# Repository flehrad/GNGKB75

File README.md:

# GNGKB75
This keyboard layout was created by goodnewsgeorge, inspired by the Eve Meteor keyboard

PCB work by flehrad

If you are producing this PCB package, it would be appreciated for attribution/crediting.

If you like this project, please consider support to The Board Podcast :)

GNGKB75_Rev0.zip is the Gerber package for production (not yet confirmed to be 100% working!)

All of the KiCAD project is in this repository including original screen images.

KiCAD v5.02-1 build was used to create this project.

Bill of materials required:

1x Elite-C microcontroller

1x Angled reset switch (MJT01117)

1x 7u stabiliser 

2x 2u stabilisers

74x 1N4148 Diode

74x MX Switches

Optional:

1x Rotary Encoder

RGB Lighting Strips (with Data/GND/VCC connections)

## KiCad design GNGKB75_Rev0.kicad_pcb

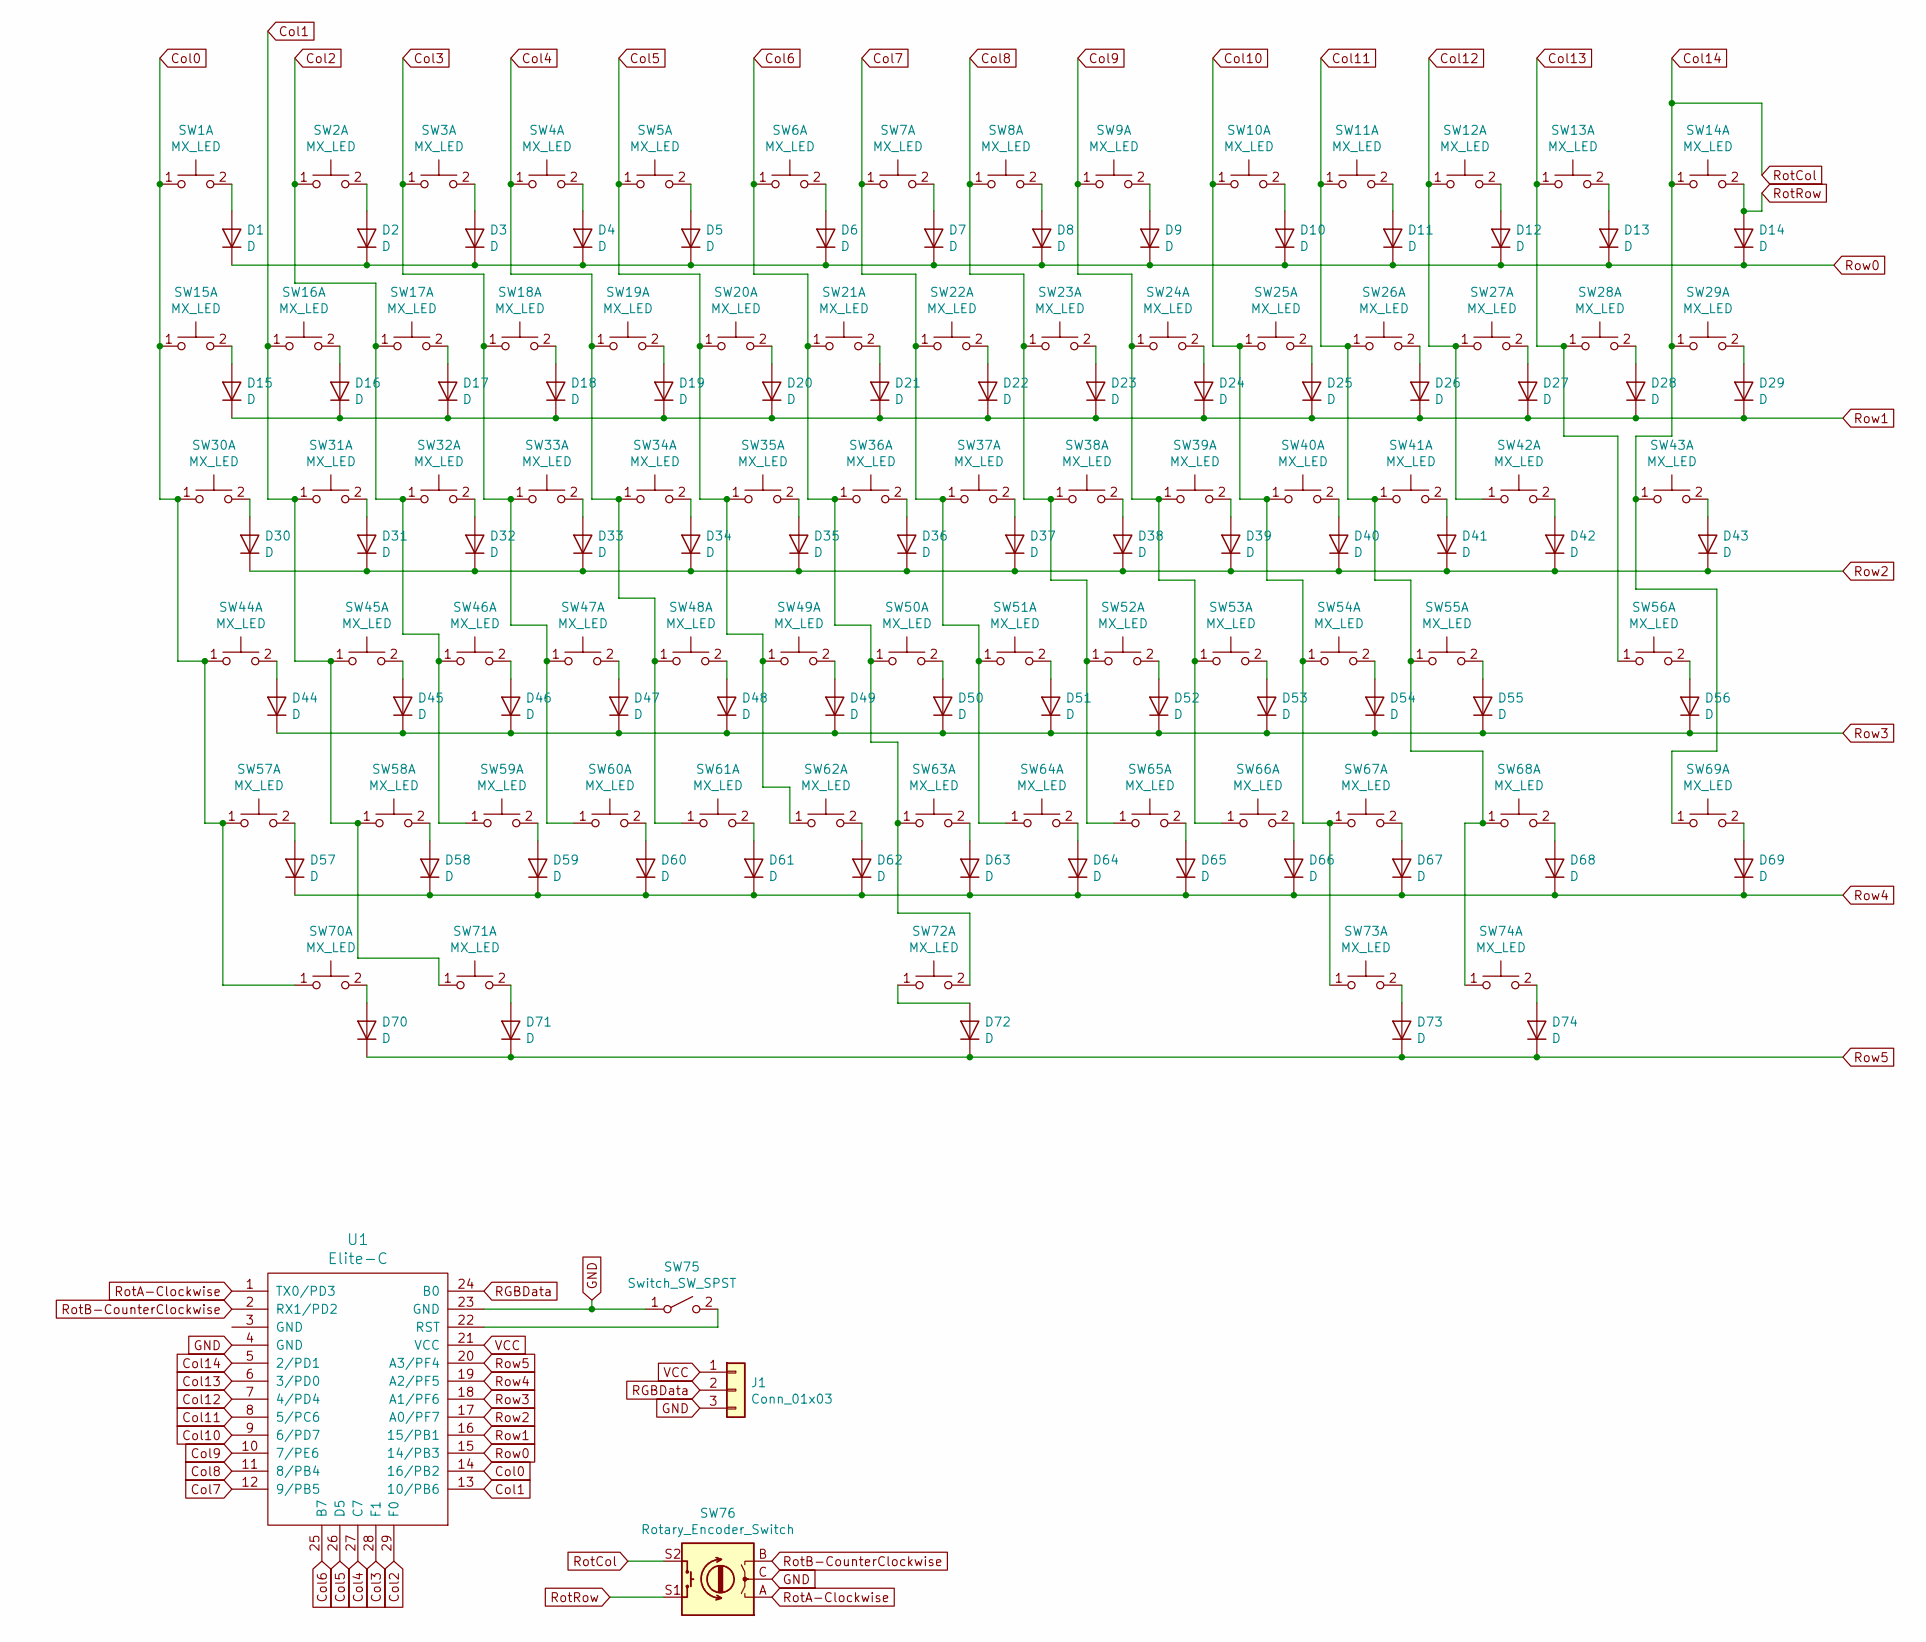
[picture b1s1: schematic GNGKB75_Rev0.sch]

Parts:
D1, D2, D3, D4, D5, D6, D7, D8, D9, D10, D11, D12, D13, D14, D15, D16, D17, D18, D19, D20, D21, D22, D23, D24, D25, D26, D27, D28, D29, D30, D31, D32, D33, D34, D35, D36, D37, D38, D39, D40, D41, D42, D43, D44, D45, D46, D47, D48, D49, D50, D51, D52, D53, D54, D55, D56, D57, D58, D59, D60, D61, D62, D63, D64, D65, D66, D67, D68, D69, D70, D71, D72, D73, D74: D; D_SOD123_axial
J1: Conn_01x03; 3_Pin_Jumper
SW1, SW2, SW3, SW4, SW5, SW6, SW7, SW8, SW9, SW10, SW11, SW12, SW13, SW14, SW15, SW16, SW17, SW18, SW19, SW20, SW21, SW22, SW23, SW24, SW25, SW26, SW27, SW28, SW29, SW31, SW32, SW33, SW34, SW35, SW36, SW37, SW38, SW39, SW40, SW41, SW42, SW45, SW46, SW47, SW48, SW49, SW50, SW51, SW52, SW53, SW54, SW55, SW58, SW59, SW60, SW61, SW62, SW63, SW64, SW65, SW66, SW67, SW69, SW70, SW74: MX_LED; Hybrid_PCB_100H_Dual_hole
SW30, SW43, SW71, SW73: MX_LED; Hybrid_PCB_150H
SW44, SW68: MX_LED; Hybrid_PCB_175H
SW56, SW57: MX_LED; Hybrid_PCB_225H
SW72: MX_LED; MX_PCB_700H
SW75: Switch_SW_SPST; SW_Tactile_SPST_Angled_MJTP1117
SW76: Rotary_Encoder_Switch; RotaryEncoder_EC11
U1: Elite-C; Elite-C-ZigZag

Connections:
Col0: SW1.1, SW15.1, SW30.1, SW44.1, SW57.1, SW70.1, U1.14 (16/PB2)
Col1: SW16.1, SW31.1, SW45.1, SW58.1, SW71.1, U1.13 (10/PB6)
Col2: SW2.1, SW17.1, SW32.1, SW46.1, SW59.1, U1.29 (F0)
Col3: SW3.1, SW18.1, SW33.1, SW47.1, SW60.1, U1.28 (F1)
Col4: SW4.1, SW19.1, SW34.1, SW48.1, SW61.1, U1.27 (C7)
Col5: SW5.1, SW20.1, SW35.1, SW49.1, SW62.1, U1.26 (D5)
Col6: SW6.1, SW21.1, SW36.1, SW50.1, SW63.1, SW72.2, U1.25 (B7)
Col7: SW7.1, SW22.1, SW37.1, SW51.1, SW64.1, U1.12 (9/PB5)
Col8: SW8.1, SW23.1, SW38.1, SW52.1, SW65.1, U1.11 (8/PB4)
Col9: SW9.1, SW24.1, SW39.1, SW53.1, SW66.1, U1.10 (7/PE6)
Col10: SW10.1, SW25.1, SW40.1, SW54.1, SW67.1, SW73.1, U1.9 (6/PD7)
Col11: SW11.1, SW26.1, SW41.1, SW55.1, SW68.1, SW74.1, U1.8 (5/PC6)
Col12: SW12.1, SW27.1, SW42.1, U1.7 (4/PD4)
Col13: SW13.1, SW28.1, SW56.1, U1.6 (3/PD0)
Col14: SW14.1, SW29.1, SW43.1, SW69.1, SW76.S2, U1.5 (2/PD1)
GND: J1.3, SW75.1 (A), SW76.C, U1.4 (GND), U1.23 (GND)
unnamed: D1.2 (A), SW1.2
unnamed: D2.2 (A), SW2.2
unnamed: D3.2 (A), SW3.2
unnamed: D4.2 (A), SW4.2
unnamed: D5.2 (A), SW5.2
unnamed: D6.2 (A), SW6.2
unnamed: D7.2 (A), SW7.2
unnamed: D8.2 (A), SW8.2
unnamed: D9.2 (A), SW9.2
unnamed: D10.2 (A), SW10.2
unnamed: D11.2 (A), SW11.2
unnamed: D12.2 (A), SW12.2
unnamed: D13.2 (A), SW13.2
unnamed: D15.2 (A), SW15.2
unnamed: D16.2 (A), SW16.2
unnamed: D17.2 (A), SW17.2
unnamed: D18.2 (A), SW18.2
unnamed: D19.2 (A), SW19.2
unnamed: D20.2 (A), SW20.2
unnamed: D21.2 (A), SW21.2
unnamed: D22.2 (A), SW22.2
unnamed: D23.2 (A), SW23.2
unnamed: D24.2 (A), SW24.2
unnamed: D25.2 (A), SW25.2
unnamed: D26.2 (A), SW26.2
unnamed: D27.2 (A), SW27.2
unnamed: D28.2 (A), SW28.2
unnamed: D29.2 (A), SW29.2
unnamed: D30.2 (A), SW30.2
unnamed: D31.2 (A), SW31.2
unnamed: D32.2 (A), SW32.2
unnamed: D33.2 (A), SW33.2
unnamed: D34.2 (A), SW34.2
unnamed: D35.2 (A), SW35.2
unnamed: D36.2 (A), SW36.2
unnamed: D37.2 (A), SW37.2
unnamed: D38.2 (A), SW38.2
unnamed: D39.2 (A), SW39.2
unnamed: D40.2 (A), SW40.2
unnamed: D41.2 (A), SW41.2
unnamed: D42.2 (A), SW42.2
unnamed: D43.2 (A), SW43.2
unnamed: D44.2 (A), SW44.2
unnamed: D45.2 (A), SW45.2
unnamed: D46.2 (A), SW46.2
unnamed: D47.2 (A), SW47.2
unnamed: D48.2 (A), SW48.2
unnamed: D49.2 (A), SW49.2
unnamed: D50.2 (A), SW50.2
unnamed: D51.2 (A), SW51.2
unnamed: D52.2 (A), SW52.2
unnamed: D53.2 (A), SW53.2
unnamed: D54.2 (A), SW54.2
unnamed: D55.2 (A), SW55.2
unnamed: D56.2 (A), SW56.2
unnamed: D57.2 (A), SW57.2
unnamed: D58.2 (A), SW58.2
unnamed: D59.2 (A), SW59.2
unnamed: D60.2 (A), SW60.2
unnamed: D61.2 (A), SW61.2
unnamed: D62.2 (A), SW62.2
unnamed: D63.2 (A), SW63.2
unnamed: D64.2 (A), SW64.2
unnamed: D65.2 (A), SW65.2
unnamed: D66.2 (A), SW66.2
unnamed: D67.2 (A), SW67.2
unnamed: D68.2 (A), SW68.2
unnamed: D69.2 (A), SW69.2
unnamed: D70.2 (A), SW70.2
unnamed: D71.2 (A), SW71.2
unnamed: D72.2 (A), SW72.1
unnamed: D73.2 (A), SW73.2
unnamed: D74.2 (A), SW74.2
unnamed: SW75.2 (B), U1.22 (RST)
RGBData: J1.2, U1.24 (B0)
RotA-Clockwise: SW76.A, U1.1 (TX0/PD3)
RotB-CounterClockwise: SW76.B, U1.2 (RX1/PD2)
RotRow: D14.2 (A), SW14.2, SW76.S1
Row0: D1.1 (K), D2.1 (K), D3.1 (K), D4.1 (K), D5.1 (K), D6.1 (K), D7.1 (K), D8.1 (K), D9.1 (K), D10.1 (K), D11.1 (K), D12.1 (K), D13.1 (K), D14.1 (K), U1.15 (14/PB3)
Row1: D15.1 (K), D16.1 (K), D17.1 (K), D18.1 (K), D19.1 (K), D20.1 (K), D21.1 (K), D22.1 (K), D23.1 (K), D24.1 (K), D25.1 (K), D26.1 (K), D27.1 (K), D28.1 (K), D29.1 (K), U1.16 (15/PB1)
Row2: D30.1 (K), D31.1 (K), D32.1 (K), D33.1 (K), D34.1 (K), D35.1 (K), D36.1 (K), D37.1 (K), D38.1 (K), D39.1 (K), D40.1 (K), D41.1 (K), D42.1 (K), D43.1 (K), U1.17 (A0/PF7)
Row3: D44.1 (K), D45.1 (K), D46.1 (K), D47.1 (K), D48.1 (K), D49.1 (K), D50.1 (K), D51.1 (K), D52.1 (K), D53.1 (K), D54.1 (K), D55.1 (K), D56.1 (K), U1.18 (A1/PF6)
Row4: D57.1 (K), D58.1 (K), D59.1 (K), D60.1 (K), D61.1 (K), D62.1 (K), D63.1 (K), D64.1 (K), D65.1 (K), D66.1 (K), D67.1 (K), D68.1 (K), D69.1 (K), U1.19 (A2/PF5)
Row5: D70.1 (K), D71.1 (K), D72.1 (K), D73.1 (K), D74.1 (K), U1.20 (A3/PF4)
VCC: J1.1, U1.21 (VCC)

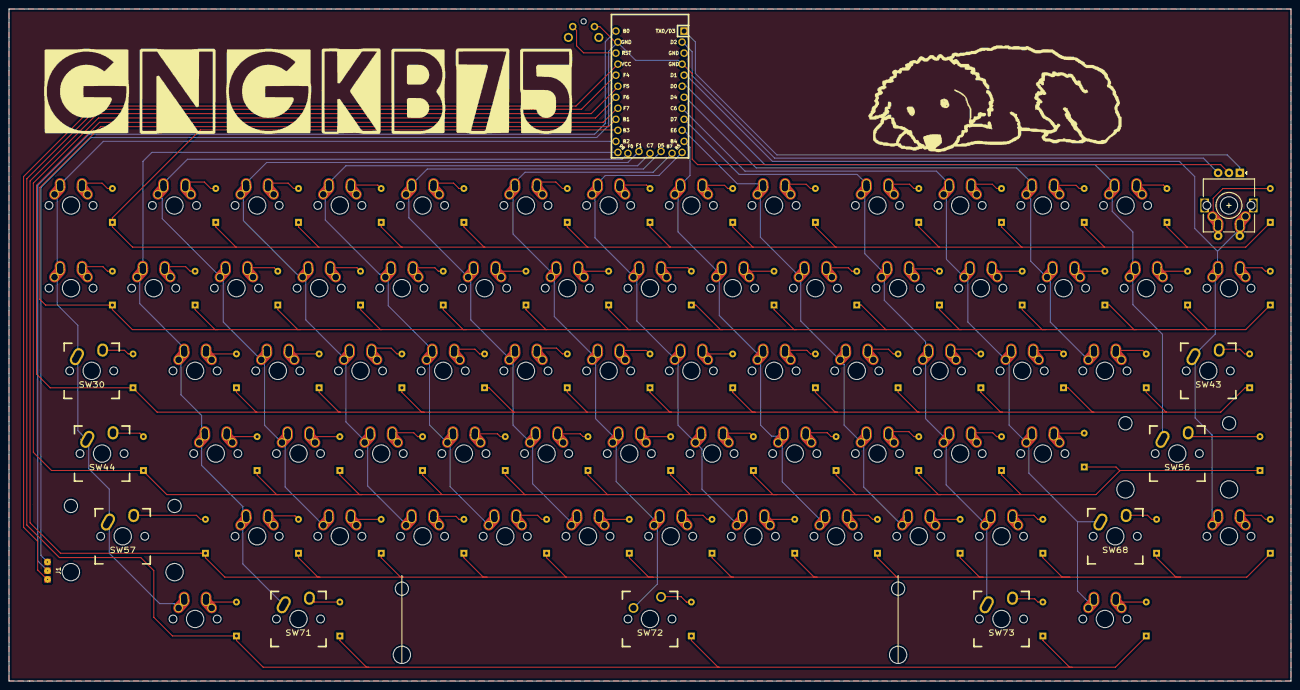
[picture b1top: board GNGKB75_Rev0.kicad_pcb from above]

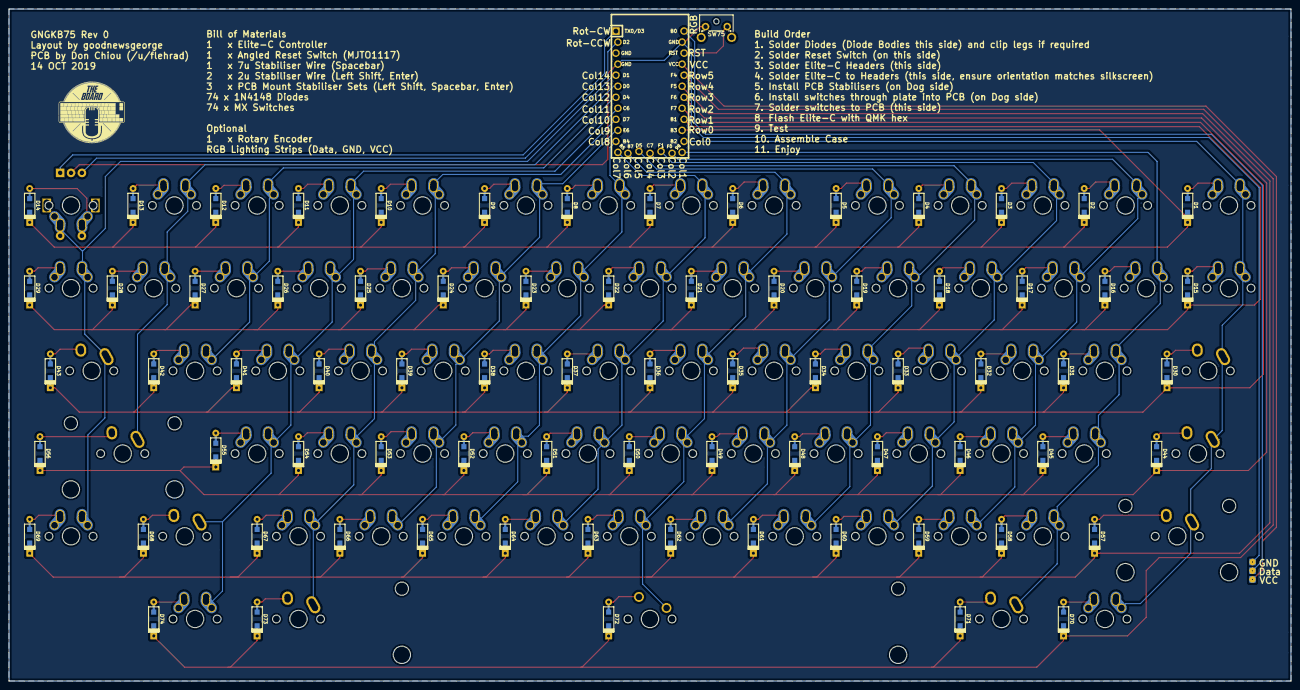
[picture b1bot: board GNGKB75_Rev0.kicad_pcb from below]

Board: 2 copper layers, 295.3 x 154.8 mm, 152 parts (76 on the bottom side), 101 nets.

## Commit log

2019-11-27 Create QMK_firmware
